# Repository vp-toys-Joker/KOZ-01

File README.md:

"# KOZ-01" 
Проект контроллера освещения и звонка
"# KOZ-01"

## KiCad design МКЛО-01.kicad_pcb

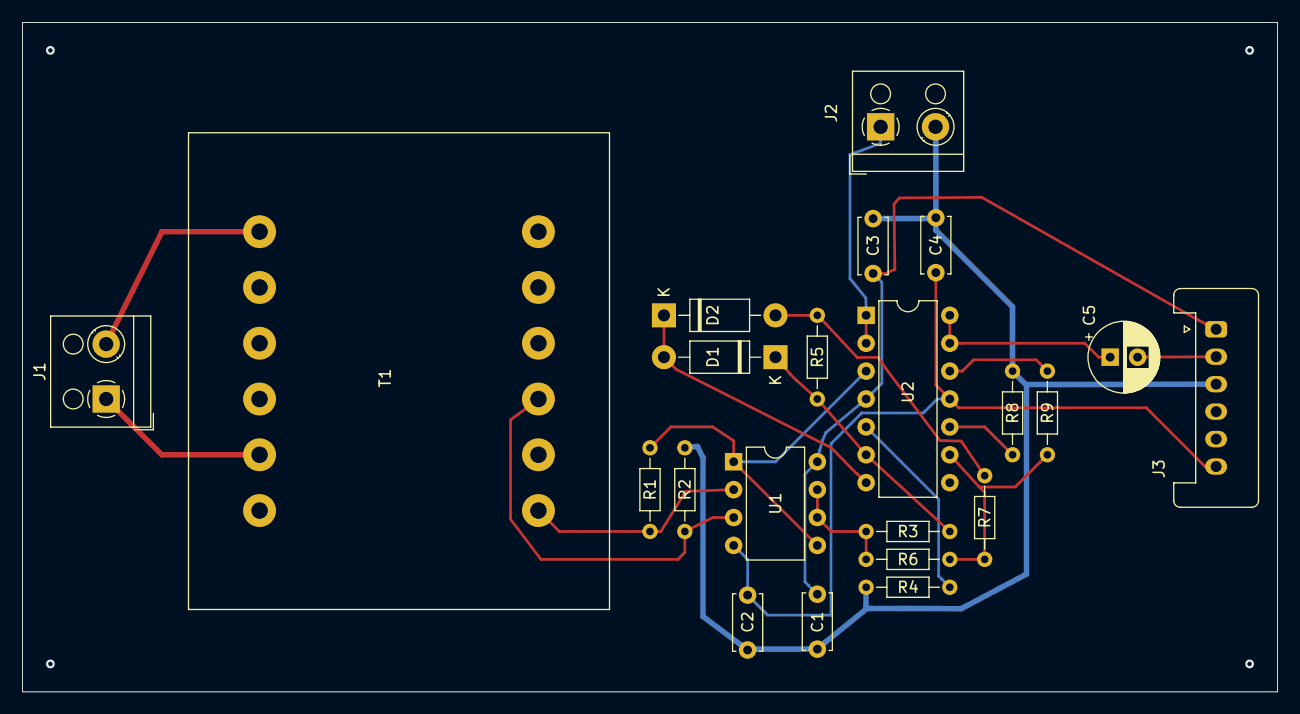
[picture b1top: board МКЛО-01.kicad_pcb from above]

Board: 2 copper layers, 114.3 x 61.0 mm, 22 parts (0 on the bottom side), 19 nets.

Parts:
C1, C2, C3, C4: 0.47; C_Disc_D5.0mm_W2.5mm_P5.00mm
C5: 10.0; CP_Radial_D6.3mm_P2.50mm
D1, D2: 1N4001; D_DO-41_SOD81_P10.16mm_Horizontal
J1, J2: Screw_Terminal_01x02; TerminalBlock_RND_205-00001_1x02_P5.00mm_Horizontal
J3: Conn_01x06_Male; Stocko_MKS_1656-6-0-606_1x6_P2.50mm_Vertical
R1, R2: 47; R_Axial_DIN0204_L3.6mm_D1.6mm_P7.62mm_Horizontal
R3, R5, R6, R9: 20k; R_Axial_DIN0204_L3.6mm_D1.6mm_P7.62mm_Horizontal
R4, R7: 10k; R_Axial_DIN0204_L3.6mm_D1.6mm_P7.62mm_Horizontal
R8: 6k8; R_Axial_DIN0204_L3.6mm_D1.6mm_P7.62mm_Horizontal
T1: Transformer_1P_1S; Transformer_37x44
U1: LF353P; DIP-8_W7.62mm
U2: LM324; DIP-14_W7.62mm

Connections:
+5V: C1.1, C3.1, J3.1, U1.8, U2.4
-5V: C2.2, C4.2, J3.6, U1.4, U2.11
GNDA: C1.2, C2.1, C3.2, C4.1, J2.2, J3.3, R1.2, R4.2, R8.2
unnamed: C5.1, U2.13, U2.14
unnamed: C5.2, J3.2
unnamed: D1.1, R3.1, R5.2, U2.6
unnamed: D1.2, D2.1, U2.7
unnamed: D2.2, R5.1, R7.2
unnamed: J1.1, T1.1
unnamed: J1.2, T1.2
unnamed: J2.1, U2.1, U2.2
unnamed: R1.1, T1.3, U1.3
unnamed: R2.1, U1.1, U1.5, U2.3
unnamed: R2.2, T1.4, U1.2
unnamed: R3.2, R6.2, U1.6, U1.7
unnamed: R4.1, U2.5
unnamed: R6.1, R7.1, R9.2, U2.9
unnamed: R8.1, U2.10
unnamed: R9.1, U2.8, U2.12

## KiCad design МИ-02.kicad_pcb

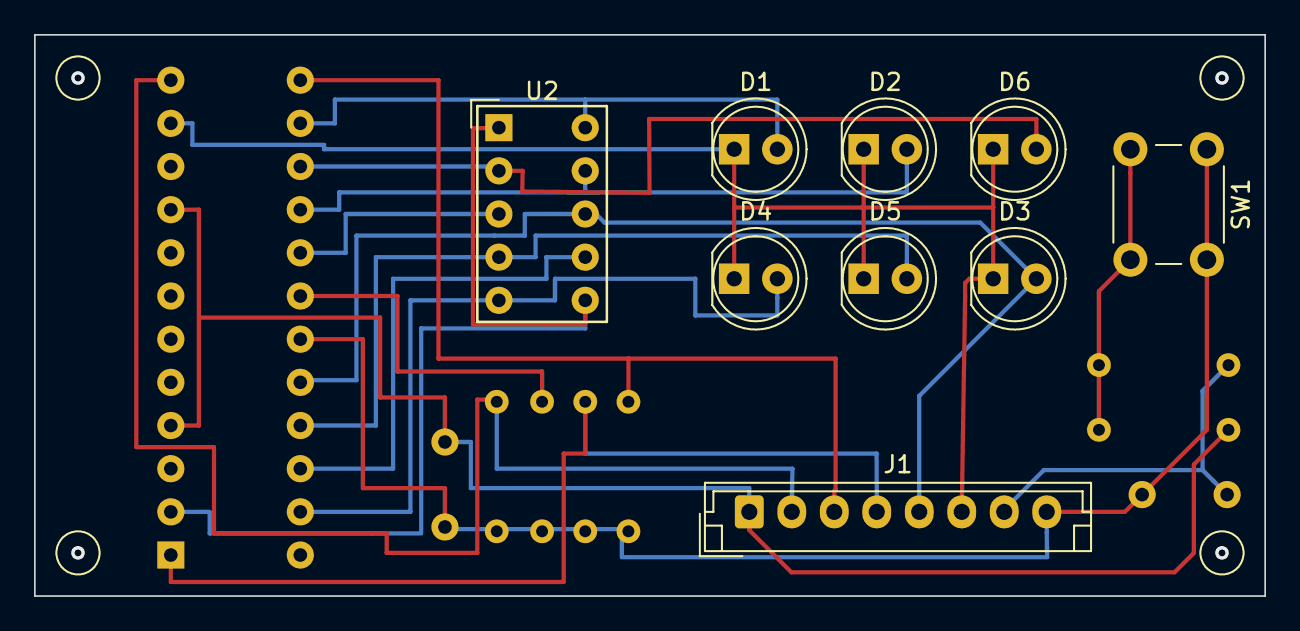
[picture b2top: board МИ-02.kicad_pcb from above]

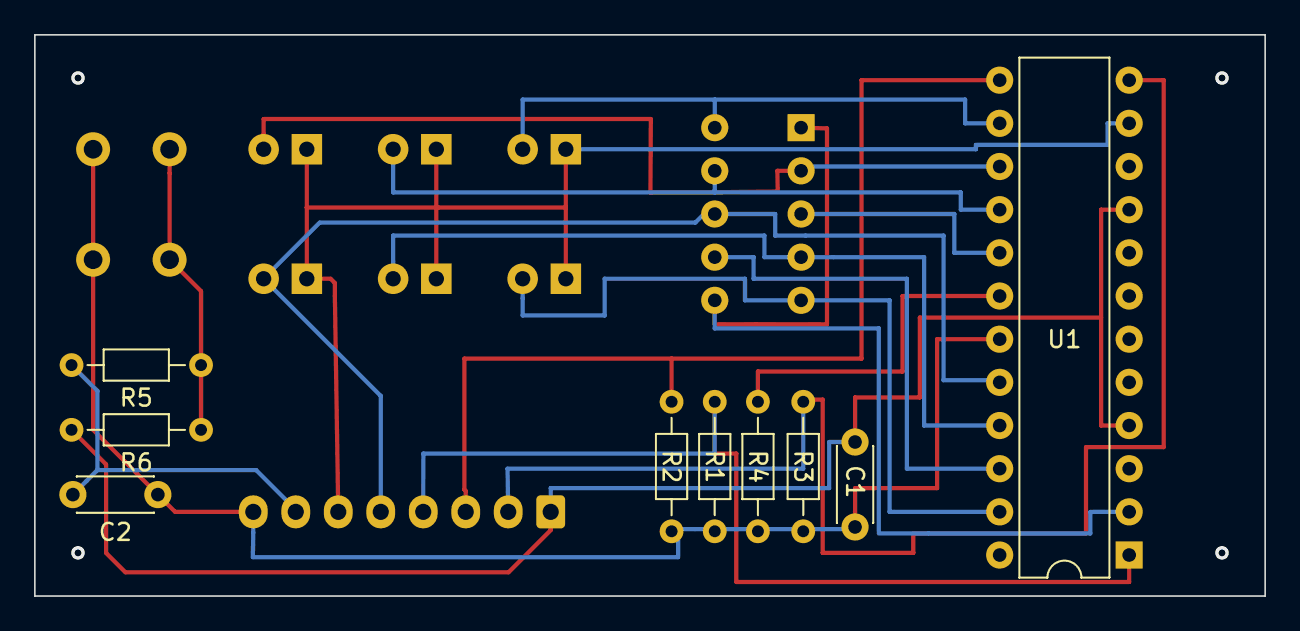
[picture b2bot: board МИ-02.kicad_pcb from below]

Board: 2 copper layers, 72.4 x 33.0 mm, 18 parts (9 on the bottom side), 16 nets.

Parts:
C1, C2: 0,1; C_Disc_D4.3mm_W1.9mm_P5.00mm
D1: 5mm LED-BLUE; LED_D5.0mm_IRGrey
D2: 5mm LED-GREEN; LED_D5.0mm_IRGrey
D3: 5mm LED-ORANGE; LED_D5.0mm_IRGrey
D4: 5mm LED-YELLOW; LED_D5.0mm_IRGrey
D5, D6: 5mm LED-RED; LED_D5.0mm_IRGrey
J1: Conn_01x08_Male; JST_EH_B8B-EH-A_1x08_P2.50mm_Vertical
R1, R2, R3, R4, R5: 10k; R_Axial_DIN0204_L3.6mm_D1.6mm_P7.62mm_Horizontal
R6: 100k; R_Axial_DIN0204_L3.6mm_D1.6mm_P7.62mm_Horizontal
SW1: "Reset"; SW_PUSH_6mm_H7.3mm
U1: MAX7221; DIP-24_W7.62mm
U2: SC36-11GWA; HDSP-A401

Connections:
+5V: C1.1, C2.1, J1.8, R1.2, R2.2, R3.2, R4.2, SW1.1
/1: D1.2, U2.10
/2: D2.2, U2.9
/3: D3.2, J1.5, U1.20, U2.8
/4: D4.2, U2.5
/5: D5.2, U2.4
/6: D6.2, U2.2
/9: U2.1, U2.6
/10: D1.1, D2.1, D3.1, D4.1, D5.1, D6.1, J1.6
/CLK: J1.3, R2.1, U1.13
/CS: J1.2, R3.1, U1.12
/DIN: J1.4, R1.1, U1.1
/RES: C2.2, J1.7, R5.2
GND: C1.2, J1.1, R6.2, U1.4, U1.9
unnamed: R4.1, U1.18
unnamed: R5.1, R6.1, SW1.2
